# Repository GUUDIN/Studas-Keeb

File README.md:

# Studas-Keeb

The idea behind this project is to create a 34 key sweep-like keyboard that costs $2 to manufacture by JLCPCB (< 100x100mm).

Initial layout renders made in KiCad have already been opened to discussion [here](https://www.reddit.com/r/ErgoMechKeyboards/comments/11aj9gn/is_this_layout_dumb/).

The main inspirations behind this project can be listed here:

 - [Cheapis](https://github.com/dotleon/cheapis): 100x10mm board with "universal" plates
 - [TOTEM](https://www.reddit.com/gallery/yzad7j?user_id=342139879532&web_redirect=true): Uses some SEED XIAOS as mcu.

Some similar projects that showed up on reddit:
 - [Bgkeep](https://github.com/sadekbaroudi/bgkeeb): 100x100mm board that uses MX spacing
 - [Zzeneg prototype](https://imgur.com/a/5ChocCR)
 - [Hypergolic](https://github.com/davidphilipbarr/hypergolic/blob/main/hyper.png)

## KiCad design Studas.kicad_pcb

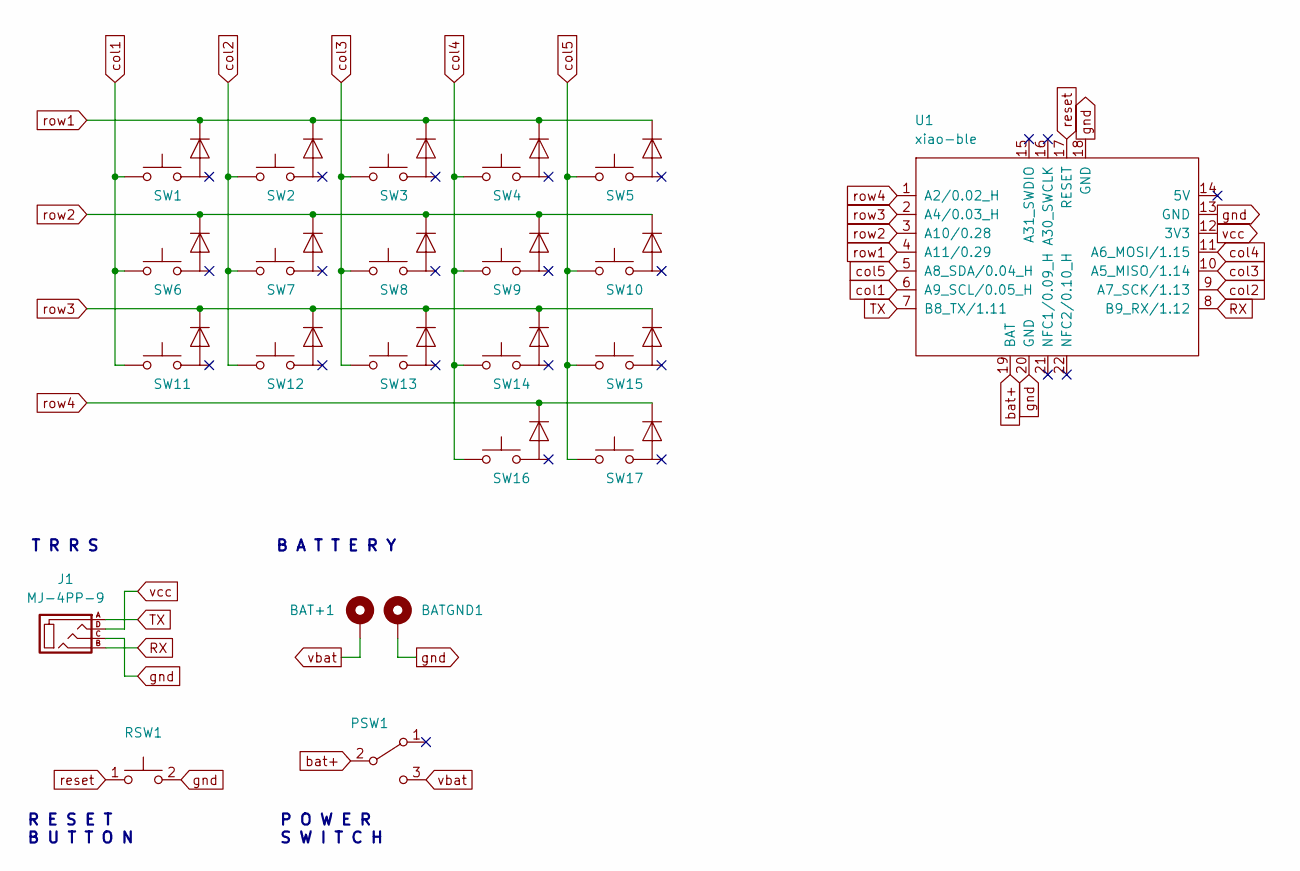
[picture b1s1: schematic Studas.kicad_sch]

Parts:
BAT+1: +; BatteryPad
BATGND1: -; BatteryPad
J1: MJ-4PP-9; MJ-4PP-9_1side
PSW1: SW_SPDT; MSK12C02
RSW1: SW_Push; SKHLLCA010
SW1, SW2, SW3, SW4, SW5, SW6, SW7, SW8, SW9, SW10, SW11, SW12, SW13, SW14, SW15, SW16, SW17: SW_Diode_Combined; SW_MX_GATLP_CHOC_reversible
U1: xiao-ble; xiao-ble-smd-cutout

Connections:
RX: J1.B, U1.8 (B9_RX/1.12)
TX: J1.A, U1.7 (B8_TX/1.11)
bat+: PSW1.2 (B), U1.19 (BAT)
col1: SW1.1, SW6.1, SW11.1, U1.6 (A9_SCL/0.05_H)
col2: SW2.1, SW7.1, SW12.1, U1.9 (A7_SCK/1.13)
col3: SW3.1, SW8.1, SW13.1, U1.10 (A5_MISO/1.14)
col4: SW4.1, SW9.1, SW14.1, SW16.1, U1.11 (A6_MOSI/1.15)
col5: SW5.1, SW10.1, SW15.1, SW17.1, U1.5 (A8_SDA/0.04_H)
gnd: BATGND1.1, J1.C, RSW1.2, U1.13 (GND), U1.18 (GND), U1.20 (GND)
reset: RSW1.1, U1.17 (RESET)
row1: SW1.3, SW2.3, SW3.3, SW4.3, SW5.3, U1.4 (A11/0.29)
row2: SW6.3, SW7.3, SW8.3, SW9.3, SW10.3, U1.3 (A10/0.28)
row3: SW11.3, SW12.3, SW13.3, SW14.3, SW15.3, U1.2 (A4/0.03_H)
row4: SW16.3, SW17.3, U1.1 (A2/0.02_H)
vbat: BAT+1.1, PSW1.3 (C)
vcc: J1.D, U1.12 (3V3)

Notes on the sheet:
P O W E R S W I T C H
B A T T E R Y
T R R S
R E S E T B U T T O N

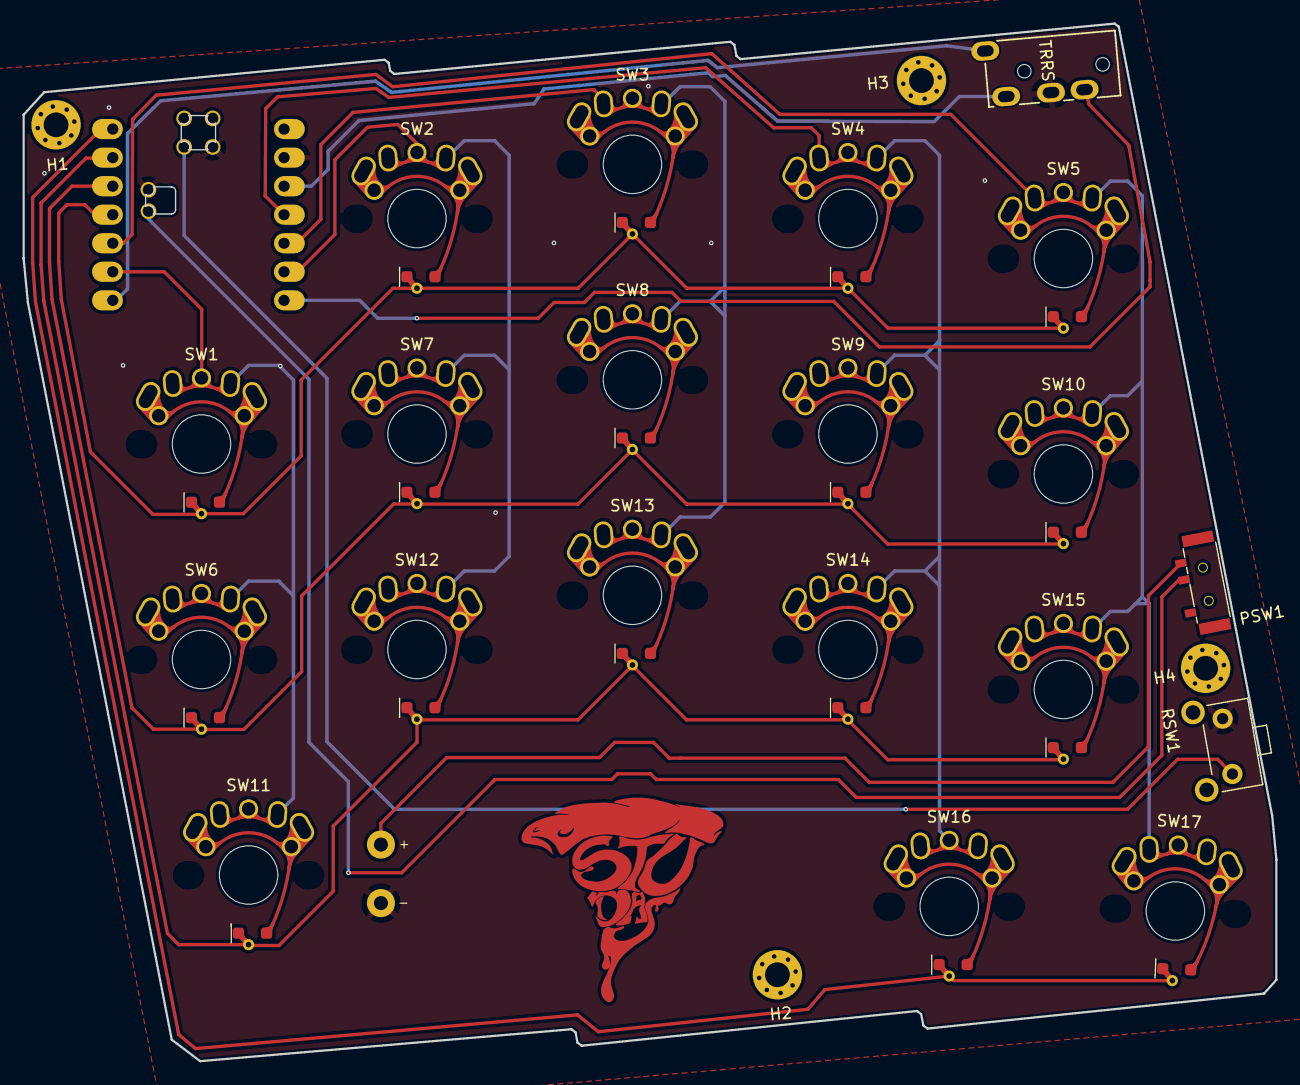
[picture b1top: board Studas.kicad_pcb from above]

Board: 2 copper layers, 111.5 x 92.3 mm, 27 parts (0 on the bottom side), 16 nets.

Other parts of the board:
H1, H2, H3, H4: MountingHole; MountingHole_2.2mm_M2_Pad_Via

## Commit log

2023-02-24 STUDAS 1.0 (not routed)
    First prototype of the keyboard, name is just a placeholder.
2023-02-24 Added libraries
2023-03-01 Case contribution
2023-03-09 Finished Routing - Ready to order
    I FINALLY ROUTED THE BOARD :)
    Added EVERY symbol/footprint used in the project.
    There are some footprint warnings that I couldn't care less.
    Suggestions for V1.2:
    - Make Switch plate board
    - Add some teardrop pads
2023-03-09 Studas_V1.1 - Ready to order
2023-03-09 Board Netlist added
2023-03-09 BOM added
